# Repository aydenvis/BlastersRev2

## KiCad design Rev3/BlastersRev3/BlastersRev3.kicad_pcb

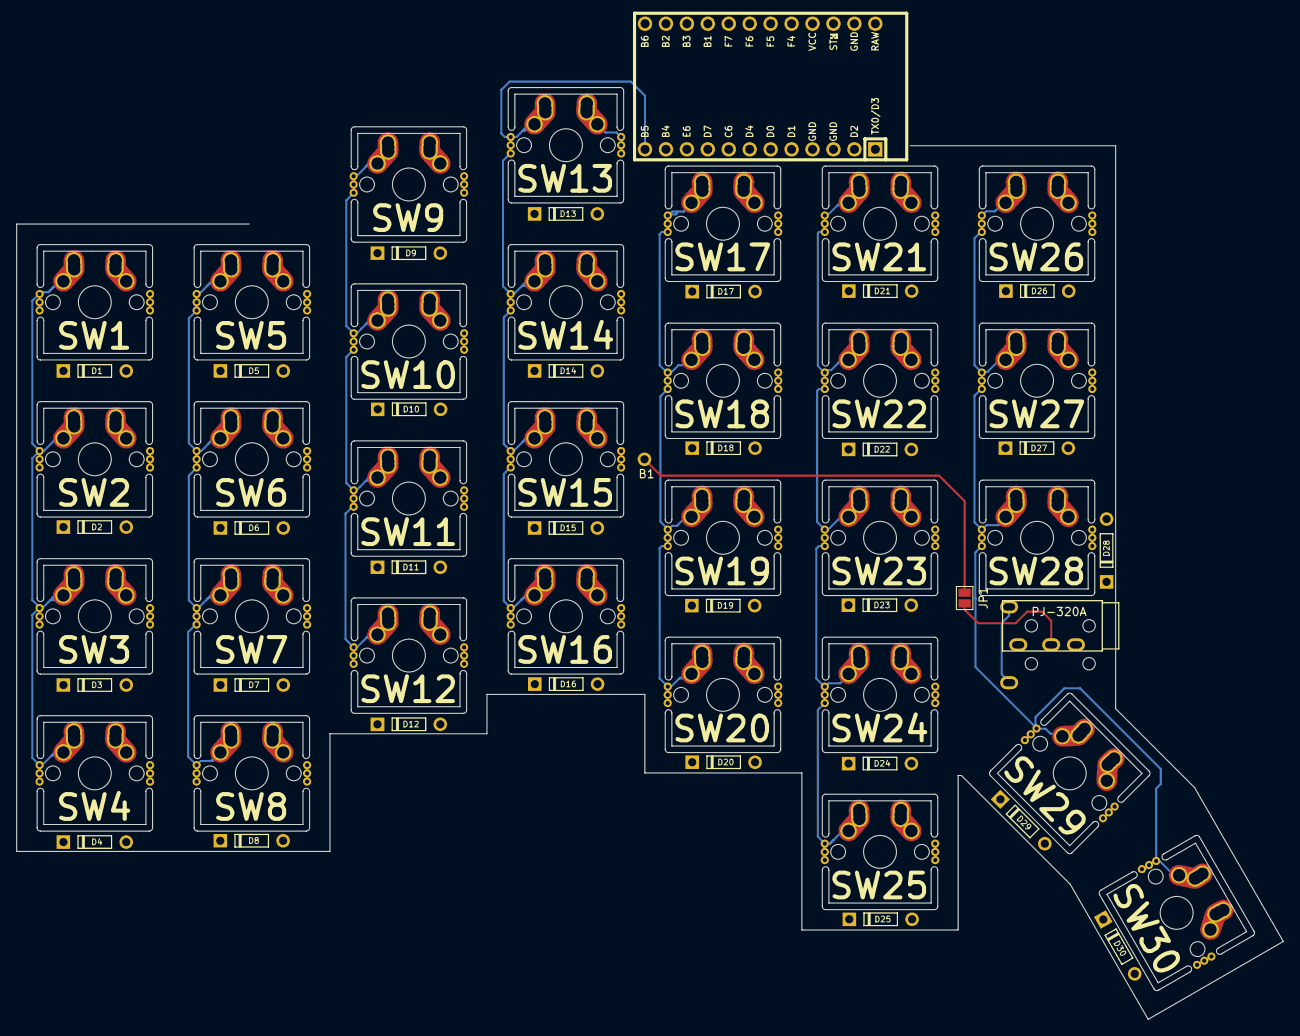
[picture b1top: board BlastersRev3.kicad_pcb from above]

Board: 2 copper layers, 153.6 x 113.0 mm, 64 parts (1 on the bottom side), 44 nets.

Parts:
B1: Breakout
D1, D2, D3, D4, D5, D6, D7, D8, D9, D10, D11, D12, D13, D14, D15, D16, D17, D18, D19, D20, D21, D22, D23, D24, D25, D26, D27, D28, D29, D30: Diode
JP1: Jumper; SolderJumper
PJ1: PJ-320A; TRRS-PJ-320A-dual
SW1, SW2, SW3, SW4, SW5, SW6, SW7, SW8, SW9, SW10, SW11, SW12, SW13, SW14, SW15, SW16, SW17, SW18, SW19, SW20, SW21, SW22, SW23, SW24, SW25, SW26, SW27, SW28, SW29, SW30: Switch; MX_Removable
U1: ProMicro

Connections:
Col0: SW1.1, SW2.1, SW3.1, SW4.1
Col1: SW5.1, SW6.1, SW7.1, SW8.1
Col2: SW9.1, SW10.1, SW11.1, SW12.1
Col3: SW13.1, SW14.1, SW15.1, SW16.1, U1.12
Col4: SW17.1, SW18.1, SW19.1, SW20.1
Col5: SW21.1, SW22.1, SW23.1, SW24.1, SW25.1
Col6: SW26.1, SW27.1, SW28.1, SW29.1, SW30.1
unnamed: D1.1, SW1.2
unnamed: D2.1, SW2.2
unnamed: D3.1, SW3.2
unnamed: D4.1, SW4.2
unnamed: D5.1, SW5.2
unnamed: D6.1, SW6.2
unnamed: D7.1, SW7.2
unnamed: D8.1, SW8.2
unnamed: D9.1, SW9.2
unnamed: D10.1, SW10.2
unnamed: D11.1, SW11.2
unnamed: D12.1, SW12.2
unnamed: D13.1, SW13.2
unnamed: D14.1, SW14.2
unnamed: D15.1, SW15.2
unnamed: D16.1, SW16.2
unnamed: D17.1, SW17.2
unnamed: D18.1, SW18.2
unnamed: D19.1, SW19.2
unnamed: D20.1, SW20.2
unnamed: D21.1, SW21.2
unnamed: D22.1, SW22.2
unnamed: D23.1, SW23.2
unnamed: D24.1, SW24.2
unnamed: D25.1, SW25.2
unnamed: D26.1, SW26.2
unnamed: D27.1, SW27.2
unnamed: D28.1, SW28.2
unnamed: D29.1, SW29.2
unnamed: D30.1, SW30.2
unnamed: JP1.1, PJ1.3
RGBBreakout: B1.1, JP1.2, U1.8
Row0: D1.2, D5.2, D9.2, D13.2, D17.2, D21.2, D26.2
Row1: D2.2, D6.2, D10.2, D14.2, D18.2, D22.2, D27.2
Row2: D3.2, D7.2, D11.2, D15.2, D19.2, D23.2, D28.2
Row3: D4.2, D8.2, D12.2, D16.2, D20.2, D24.2, D29.2
Row4: D25.2, D30.2

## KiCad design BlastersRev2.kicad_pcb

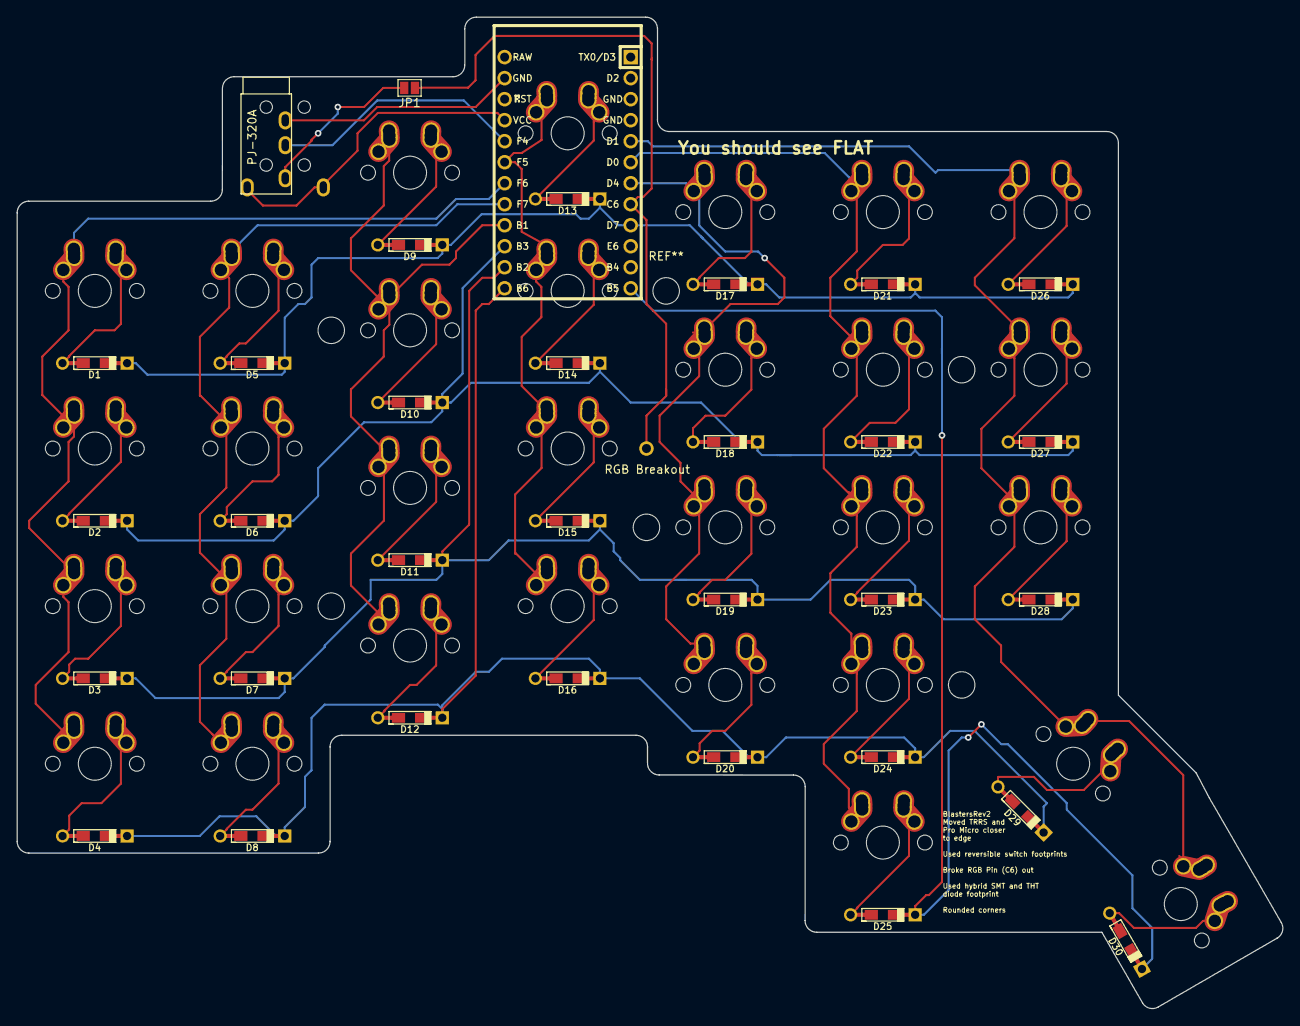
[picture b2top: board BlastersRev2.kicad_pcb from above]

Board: 2 copper layers, 153.0 x 119.8 mm, 64 parts (1 on the bottom side), 43 nets.

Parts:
D1, D2, D3, D4, D5, D6, D7, D8, D9, D10, D11, D12, D13, D14, D15, D16, D17, D18, D19, D20, D21, D22, D23, D24, D25, D26, D27, D28, D29, D30: D_Small; Diode-dual
J1: AudioJack4_Ground; TRRS-PJ-320A-dual
JP1: Jumper; SolderJumper-2_P1.3mm_Open_Pad1.0x1.5mm
MX1, MX2, MX3, MX4, MX5, MX6, MX7, MX8, MX9, MX10, MX11, MX12, MX13, MX14, MX15, MX16, MX17, MX18, MX19, MX20, MX21, MX22, MX23, MX24, MX25, MX26, MX27, MX28, MX29, MX30: MX-NoLED; Hybrid_PCB_100H_Dual_hole
RGB Data: MountingHole
U1: ProMicro; ArduinoProMicro

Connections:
Col0: MX1.1, MX2.1, MX3.1, MX4.1, U1.18
Col1: MX5.1, MX6.1, MX7.1, MX8.1, U1.17
Col2: MX9.1, MX10.1, MX11.1, MX12.1, U1.16
Col3: MX13.1, MX14.1, MX15.1, MX16.1, U1.19
Col4: MX17.1, MX18.1, MX19.1, MX20.1, U1.7
Col5: MX21.1, MX22.1, MX23.1, MX24.1, MX25.1, U1.6
Col6: MX26.1, MX27.1, MX28.1, MX29.1, MX30.1, U1.5
unnamed: D1.2, MX1.2
unnamed: D2.2, MX2.2
unnamed: D3.2, MX3.2
unnamed: D4.2, MX4.2
unnamed: D5.2, MX5.2
unnamed: D6.2, MX6.2
unnamed: D7.2, MX7.2
unnamed: D8.2, MX8.2
unnamed: D9.2, MX9.2
unnamed: D10.2, MX10.2
unnamed: D11.2, MX11.2
unnamed: D12.2, MX12.2
unnamed: D13.2, MX13.2
unnamed: D14.2, MX14.2
unnamed: D15.2, MX15.2
unnamed: D16.2, MX16.2
unnamed: D17.2, MX17.2
unnamed: D18.2, MX18.2
unnamed: D19.2, MX19.2
unnamed: D20.2, MX20.2
unnamed: D21.2, MX21.2
unnamed: D22.2, MX22.2
unnamed: D23.2, MX23.2
unnamed: D24.2, MX24.2
unnamed: D25.2, MX25.2
unnamed: D26.2, MX26.2
unnamed: D27.2, MX27.2
unnamed: D28.2, MX28.2
unnamed: D29.2, MX29.2
unnamed: D30.2, MX30.2
RGBCommBreakout: JP1.1, U1.8
Row0: D1.1, D5.1, D9.1, D13.1, D17.1, D21.1, D26.1, U1.9
Row1: D2.1, D6.1, D10.1, D14.1, D18.1, D22.1, D27.1, U1.15
Row2: D3.1, D7.1, D11.1, D15.1, D19.1, D23.1, D28.1, U1.14
Row3: D4.1, D8.1, D12.1, D16.1, D20.1, D24.1, D29.1, U1.13
Row4: D25.1, D30.1, U1.12

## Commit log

2019-06-17 Created Kicad files
2019-06-17 Add submodule
2019-06-17 Added footprint and pretty libraries
2019-06-17 SCH file complete
2019-06-17 All components placed
2019-06-18 Done!
2019-06-20 Generated gerbers and added soldermask commentary
2019-06-20 Zipped production files
2019-06-26 Rev3 begins
2019-06-27 Preliminary col routing done
